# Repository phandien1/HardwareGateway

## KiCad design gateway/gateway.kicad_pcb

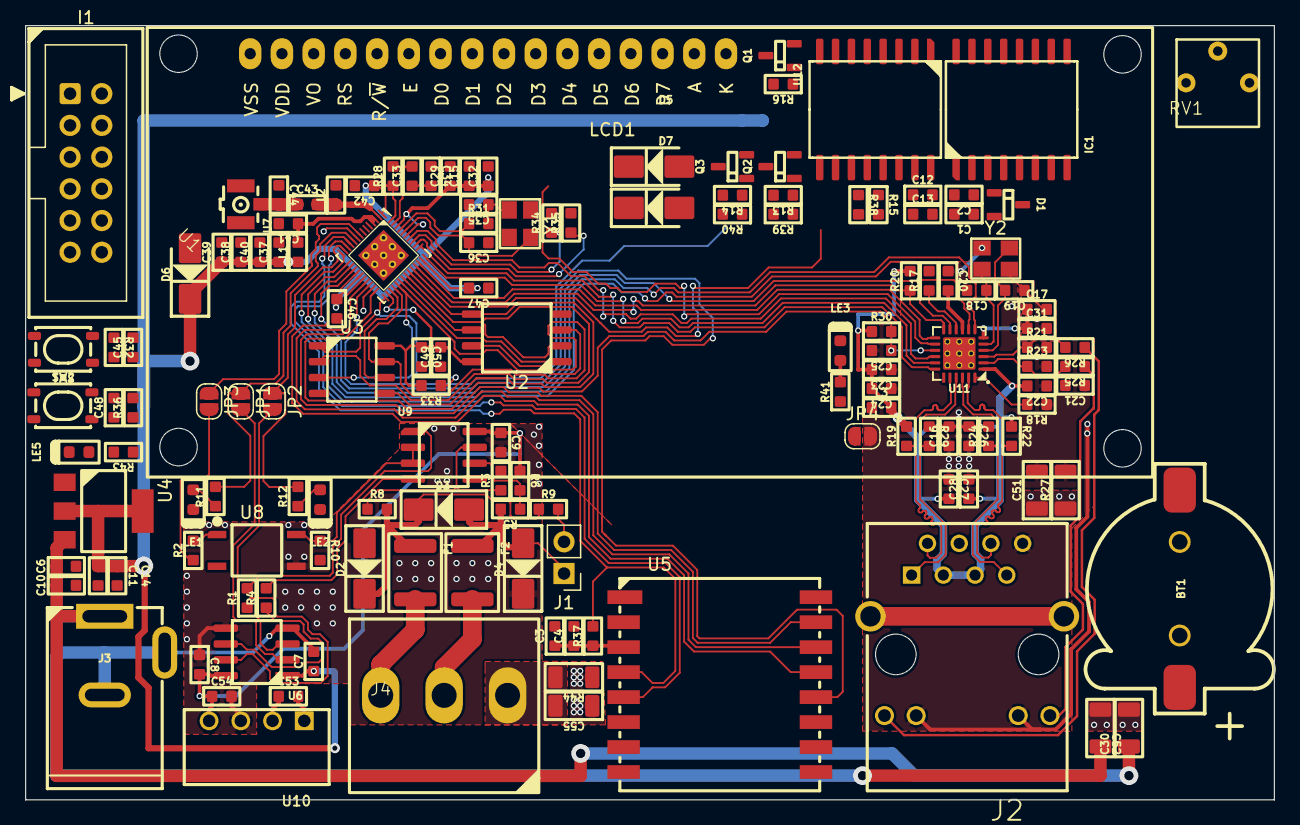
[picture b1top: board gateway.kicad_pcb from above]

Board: 2 copper layers, 100.0 x 62.0 mm, 144 parts (0 on the bottom side), 98 nets.

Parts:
BT1: CR1220; BatteryHolder_CR1220
C1, C3, C6, C11, C12, C25, C39, C45, C48, C54: 10uF_50V; C_0603
C2, C4, C7, C8, C9, C13, C20, C21, C22, C23, C24, C27, C28, C32, C37, C40, C41, C42, C46, C47: 100nF_50V; C_0603
C10, C14, C16, C26, C29, C31, C38, C49, C50: 1uF_50V; C_0603
C15: 100pF_50V; C_0603
C17: 470pF_50V; C_0603
C18, C19, C35, C36: 20pF_50V; C_0603
C30, C51, C52, C55: 10nF_50V; C_1206
C33: 3.3nF_50V; C_0603
C34: 10nF_50V; C_0603
C43: 5.6pF_50V; C_0603
C44: NC; C_0603
C53: 4.7uF_50V; C_0603
D1: BAT54C; SOT23-3
D2, D3, D4, D6: D_TVS; D_SMA
D5, D7: D_Schottky; D_SMA
F1, F2: Polyfuse; Fuse_1812_4532Metric
I1: Conn_IDC_2X6; IDC-Header_2x06_P2.54mm_Vertical
IC1: RTC_DS3231M; SOIC-16W_7.5x10.3mm_P1.27mm
J1: PinHeader_1x02_P2.54mm_Vertical
J2: HR915310A; Ethernet-Conn_HR911105A
J3: Barrel_Jack_Switch; DC_PowerJack_5mm_THT
J4: Screw_Terminal_01x03; KF103-3pin-5.08mm
JP1, JP2, JP3, JP4: SolderJumper-2_P1.3mm_Open_RoundedPad1.0x1.5mm
L1, L3: 2.2nH_1A; L_0603
L2: NC; L_0603
LCD1: LCD_HD44780
LE1, LE2, LE3, LE5: Led; LED0603
Q1, Q2, Q3: SI2300; SOT23-3
R1, R4, R5, R8, R9: 120R_1%_0.1W; R_0603
R2, R11, R12: 1k_1%_0.1W; R_0603
R3, R6, R10: 10k_1%_0.1W; R_0603
R13, R14, R15, R17, R20, R21, R23, R30, R32, R33, R36, R37, R38, R39, R40: 4k7_1%_0.1W; R_0603
R16: 1M_1%_0.1W; R_0603
R18: 12k_1%_0.1W; R_0603
R19, R22, R24, R29: 49R9_1%_0.1W; R_0603
R25, R26, R41: 470R_1%_0.1W; R_0603
R27, R44: 1M_1%; R_1206
R28: 20k_1%_0.1W; R_0603
R31, R35: 0R_1%_0.1W; R_0603
R34: 490R_1%_0.1W; R_0603
R43: 1k5_1%_0.1W; R_0603
RV1: R_Potentiometer; R-potimeter-3pin
SW1, SW2: SW_Tactile; SW_SPST_PTS810
U1: ESP32_D0WD_V3_SOC
U2: GD25Q32CSIG; SOP-8_5.28x5.23mm_P1.27mm
U3: LY68L6400SLIT; SOP-8_3.9x4.9mm_P1.27mm
U4: AMS1117; SOT233
U5: RF_Module_Ai-Thinker-Ra-02; MODULE_RA-02_LORA
U6: ISO7721DR; SOIC-8_3.9x4.9mm_P1.27mm
U7: Ipex; Conn_IPEX_ANT
U8: UL357; OPTO_EL357N-G
U9: MAX485E; SOIC-8_3.9x4.9mm_P1.27mm
U10: B0505S; Powersupply_B0505S-1W
U11: LAN8720A-CP; QFN-24_4x4_PAD-VIAS
U12: PCF8574; SOIC-16W_7.5x10.3mm_P1.27mm
Y1: 40Mhz; Crystal_SMD_3225-4Pin_3.2x2.5mm
Y2: 25Mhz; Crystal_SMD_3225-4Pin_3.2x2.5mm

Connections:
+3V3: C1.1, C2.1, C3.1, C4.1, C7.1, C11.1, C14.1, C15.1, C20.2, C29.1, C32.1, C37.1, C38.1, C39.1, C40.1, C42.1, C46.1, C47.2, D1.1, D6.1, I1.11, IC1.2 (VCC), L1.1, L3.1, Q2.1 (G), Q3.1 (G), R13.1, R14.1, R15.1, R32.1, R36.1, R37.1, R38.1, R41.1, R43.1, U1.1 (VDDA_1), U1.19 (VDD3P3_RTC), U1.37 (VDD3P3_CPU), U1.43 (VDDA_2), U1.46 (VDDA_3), U4.2 (VO), U5.3 (VDD), U6.1 (VCC1), U11.9 (VDDIO)
+5V: C6.1, C10.1, C12.2, C13.2, C30.1, C53.1, I1.12, J3.1, LCD1.2 (VDD), LCD1.15 (LEDA), R39.1, R40.1, RV1.1, U4.3 (VI), U10.2 (Vin), U12.16 (VDD)
+5VA: C8.2, C9.1, C54.1, R6.1, R10.2, U6.8 (VCC2), U9.8 (VCC), U10.4 (Vout)
/Ethernet/ETH_LED1: R21.1, R26.2, U11.3 (LED1/~REGOFF)
/Ethernet/ETH_LED2: R23.1, R25.2, U11.2 (LED2/~NINTSEL)
/Ethernet/PHY_RXD+: J2.6 (RD+), R22.2, U11.23 (RXP)
/Ethernet/PHY_RXD-: J2.7 (RD-), R24.1, U11.22 (RXN)
/Ethernet/PHY_TXD+: J2.1 (TD+), R29.2, U11.21 (TXP)
/Ethernet/PHY_TXD-: J2.2 (TD-), R19.1, U11.20 (TXN)
/Ethernet/PHY_nRST: C25.1, LE3.2, R30.2, U1.24 (GPIO4), U11.15 (NRST)
/Ethernet/RMII_CRS_DV: U1.16 (GPIO27), U11.11 (CRS_DV/~MODE2)
/Ethernet/RMII_MDC: U1.36 (GPIO23), U11.13 (MDC)
/Ethernet/RMII_MDIO: R20.1, U1.35 (GPIO18), U11.12 (MDIO)
/Ethernet/RMII_RXD0: U1.14 (GPIO25), U11.8 (RXD0/~MODE0)
/Ethernet/RMII_RXD1: U1.15 (GPIO26), U11.7 (RXD1/~MODE1)
/Ethernet/RMII_TXD0: U1.38 (GPIO19), U11.17 (TXD0)
/Ethernet/RMII_TXD1: U1.39 (GPIO22), U11.18 (TXD1)
/Ethernet/RMII_TXEN: U1.42 (GPIO21), U11.16 (TXEN)
/LCD20x4/SCL: IC1.16 (SCL), Q2.2 (S), Q2.3 (D), R13.2, R15.2, R39.2, U1.34 (GPIO5), U12.14 (SCL)
/LCD20x4/SDA: D7.1, IC1.15 (SDA), Q3.2 (S), Q3.3 (D), R14.2, R38.2, R40.2, U1.22 (GPIO2), U12.15 (SDA)
/LoRa/RA_DIO0: U1.12 (32K_XP), U5.5 (DIO0)
/LoRa/RA_RST: R37.2, U1.11 (VDET_2), U5.4 (~RESET)
/MCU/BOOT: D5.1, I1.1, U1.23 (GPIO0), U11.14 (NINT/REFCLKO)
/MCU/GPIO39: JP3.1 (A), U1.8 (SENSOR_VN)
/MCU/MRST: C45.1, I1.3, R32.2, SW1.2, U1.9 (CHIP_PU)
/MCU/MTCK: I1.4, U1.20 (MTCK), U5.14 (MOSI)
/MCU/MTDI: I1.8, U1.18 (MTDI), U5.13 (MISO)
/MCU/MTDO: I1.6, U1.21 (MTDO), U5.15 (~NSS)
/MCU/MTMS: I1.2, U1.17 (MTMS), U5.12 (SCK)
/MCU/SCK_CLK: U1.31 (SD_CLK), U2.6 (SCLK)
/MCU/SCS_CMD: U1.30 (SD_CMD), U2.1 (CS#)
/MCU/SDI_SD1: U1.33 (SD_DATA_1), U2.5 (SI_(IO0)), U3.5 (SI/SIO[0])
/MCU/SDO_SD0: U1.32 (SD_DATA_0), U2.2 (SO_(IO1)), U3.2 (SO/SIO[1])
/MCU/SHD_SD2: U1.28 (SD_DATA_2), U2.7 (HOLD#_(IO3)), U3.7 (SIO[3])
/MCU/SRAM_CLK: U1.27 (GPIO17), U3.6 (SCLK)
/MCU/SRAM_CS: R33.1, U1.25 (GPIO16), U3.1 (CE#)
/MCU/SWP_SD3: U1.29 (SD_DATA_3), U2.3 (WP#_(IO2)), U3.3 (SIO[2])
/RS485/MAX485_RX: JP2.1 (A), R12.2, U1.13 (32K_XN)
/RS485/MAX485_TX: JP1.1 (A), R11.2, U1.10 (VDET_1)
/RS485/ctr: R10.1, U8.4, U9.2 (~RE), U9.3 (DE)
A+: F2.2, J4.2
B-: F1.2, J4.1
EARTH: C30.2, C51.1, C52.1, J2.SH (SHIELD), R27.1
Earth: C55.2, J4.3, R44.2
GND: BT1.2 (-), C1.2, C2.2, C3.2, C4.2, C6.2, C7.2, C10.2, C11.2, C12.1, C13.1, C14.2, C15.2, C29.2, C32.2, C34.1, C35.2, C36.1, C37.2, C38.2, C39.2, C40.2, C41.2, C42.2, C44.1, C45.2, C46.2, C47.1, C48.2, C49.1, C50.2, C52.2, C53.2, D6.2, I1.9, I1.10, IC1.5 (GND), IC1.6 (GND), IC1.7 (GND), IC1.8 (GND), IC1.9 (GND), IC1.10 (GND), IC1.11 (GND), IC1.12 (GND), IC1.13 (GND), J3.2, J3.3, JP4.1 (A), L2.2, LCD1.1 (VSS), LE1.2, LE2.2, LE5.2, Q1.2 (S), R16.2, RV1.3, SW1.1, SW2.1, U1.49 (GND), U2.4 (VSS), U3.4 (VSS), U4.1 (GND), U5.1 (GND), U5.2 (GND), U5.9 (GND), U5.16 (GND), U6.4 (GND1), U7.2, U7.3, U8.2, U10.1 (GNDin), U12.1 (A0), U12.2 (A1), U12.3 (A2), U12.8 (VSS), Y1.2, Y1.4
GNDA: C8.1, C9.2, C54.2, C55.1, D2.2, D4.1, R3.2, R44.1, U6.5 (GND2), U8.3, U9.5 (GND), U10.3 (GNDout)
GND_ETH: C16.1, C17.2, C18.2, C19.1, C20.1, C21.1, C22.1, C23.1, C24.1, C25.2, C26.2, C27.1, C28.2, C31.2, C51.2, J2.8 (GND), J2.10 (LEDG_K), J2.11 (LEDY_K), JP4.2 (B), R17.2, R18.1, R21.2, R23.2, R27.2, U11.25 (EPAD), Y2.2, Y2.4
unnamed: BT1.1 (+), D1.2
unnamed: C35.1, R31.2, Y1.1
unnamed: C43.1, C44.2, U7.1
unnamed: C48.1, D5.2, D7.2, R36.2, SW2.2
unnamed: D2.1, D3.1, F1.1, R8.2, R9.1
unnamed: I1.5, R34.2
unnamed: I1.7, R35.2
unnamed: D1.3, IC1.14 (VBAT)
unnamed: D3.2, D4.2, F2.1, J1.1, R5.2
unnamed: J1.2, R9.2
unnamed: J2.9 (LEDG_A), R26.1
unnamed: J2.12 (LEDY_A), R25.1
unnamed: JP1.2 (B), U6.2 (OUTA)
unnamed: JP2.2 (B), U6.3 (INB)
unnamed: JP3.2 (B), R2.1
unnamed: LCD1.11 (DB4), U12.7 (P3)
unnamed: LCD1.12 (DB5), U12.9 (P4)
unnamed: LCD1.13 (DB6), U12.10 (P5)
unnamed: LCD1.14 (DB7), U12.11 (P6)
unnamed: LCD1.6 (E), U12.4 (P0)
unnamed: LCD1.16 (LEDK), Q1.3 (D)
unnamed: LCD1.4 (RS), U12.6 (P2)
unnamed: LCD1.5 (R/~W), U12.5 (P1)
unnamed: LCD1.3 (Vo), RV1.2
unnamed: LE1.1, R11.1
unnamed: LE2.1, R12.1
unnamed: LE3.1, R41.2
unnamed: LE5.1, R43.2
unnamed: Q1.1 (G), R16.1, U12.12 (P7)
unnamed: R2.2, U8.1
unnamed: C33.1, C34.2, R28.1, U1.48 (CAP1)
unnamed: C33.2, R28.2, U1.47 (CAP2)
unnamed: C43.2, L2.1, U1.2 (LNA_IN)
unnamed: R35.1, U1.40 (U0RXD)
unnamed: R34.1, U1.41 (U0TXD)
unnamed: C41.1, L1.2, U1.3 (VDD3P3_1), U1.4 (VDD3P3_2)
unnamed: C49.2, C50.1, R33.2, U1.26 (VDD_SDIO), U2.8 (VCC), U3.8 (VCC)
unnamed: C36.2, U1.44 (XTAL_N), Y1.3
unnamed: R31.1, U1.45 (XTAL_P)
unnamed: R1.1, U6.7 (INA)
unnamed: R4.1, U6.6 (OUTB)
unnamed: R5.1, R6.2, U9.6 (A)
unnamed: R3.1, R8.1, U9.7 (B)
unnamed: R4.2, U9.4 (DI)
unnamed: R1.2, U9.1 (RO)
unnamed: R18.2, U11.24 (RBIAS)
unnamed: R17.1, U11.10 (RXER/~PHYAD0)
unnamed: C17.1, C31.1, U11.6 (VDDCR)
unnamed: C18.1, U11.5 (XTAL1/CLKIN), Y2.1
unnamed: C19.2, U11.4 (XTAL2), Y2.3
VDD_ETH: C16.2, C21.2, C22.2, C23.2, C24.2, C26.1, C27.2, C28.1, J2.3 (TCT), J2.5 (RCT), L3.2, R19.2, R20.2, R22.1, R24.2, R29.1, R30.1, U11.1 (VDD2A), U11.19 (VDD1A)

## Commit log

2023-04-19 create new file

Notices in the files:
parts and their libraries:
Copyright 2021 Accelerated Designs. All rights reserved.
